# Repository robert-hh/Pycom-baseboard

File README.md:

Baseboard: Simple baseboard for PyCom development modules

This board does not use SMD components. Instead low price modules for the USB/UART
bridge and the SD card adapter are used. The USB/UART bridge is the red FTDI
module, which are sold at prices of $1.5 on. It has to be set to 3.3 V.
The SD card module is the one of Pololu, which is also widely available.
Pictures of the modules are included in the repository. Depending on the
soldered connectors, the board can also be used for WiPy1. Artwork on the board indicates, how the Pycom modules have to be inserted.

The board also carries the two transistor logic used by espressif to switch into
bootstrap mode. The Pycom command line updater pycom-fwtool-cli supports that
with the -r option. The graphical variant does not. If you are building The
firmware yourself, you have to change application.mk at the command for
flashing. Change it into:

  ESPTOOLPY_SERIAL = $(ESPTOOLPY) --port $(ESPPORT) --baud $(ESPBAUD)

especially, remove  "--before no_reset --after no_reset"

Also on the board:
- connections for a reset button, if the board is placed into a closed box.
- A JST2 connector for a battery. There is no charging circuit on the board,
but a diode is foreseen to decouple the battery from the USB/UART bridge. If
you do not need that, solder a wire. Depending on your preference, a Schottky
diode or a silicon diode can be used. Schottky diodes have a substantial
reverse current.  

The metal areas at the mounting holes are connected to GND. That is favorable
if you put the whole board into a metal box, used as ground plane for a Lora or
LTE antenna. If that gets a problem, use Nylon screws.

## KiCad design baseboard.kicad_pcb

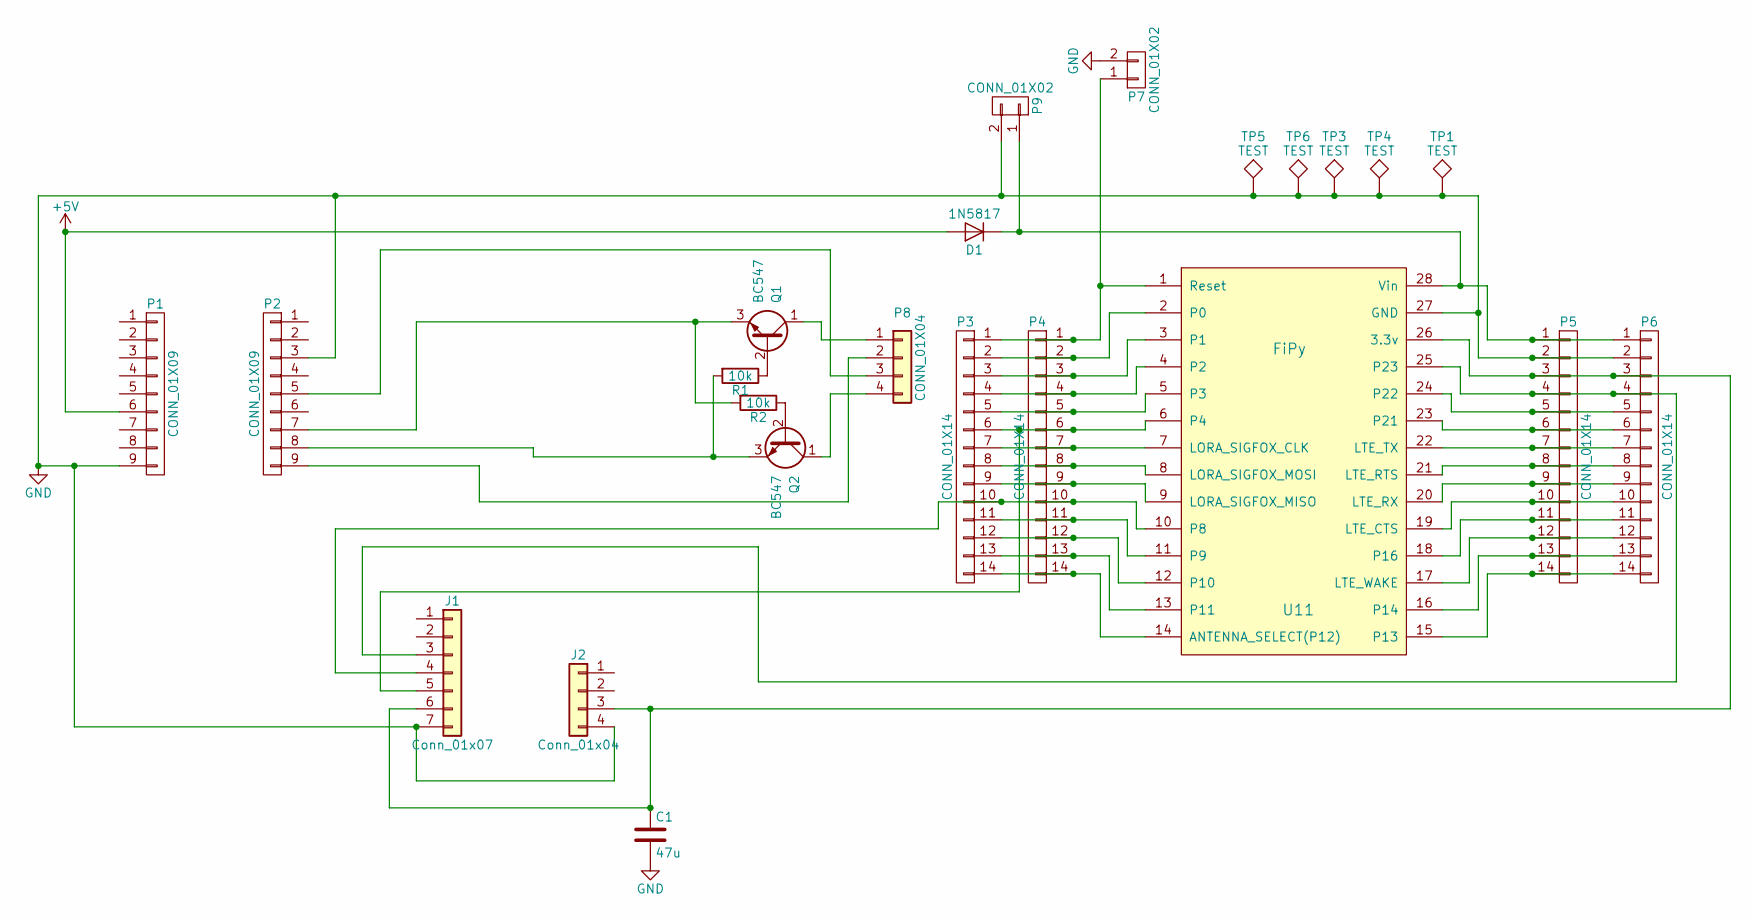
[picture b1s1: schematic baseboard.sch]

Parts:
C1: 47u; CP_Radial_D6.3mm_P2.50mm
D1: 1N5817; D_DO-41_SOD81_P10.16mm_Horizontal
J1: Conn_01x07; Socket_Strip_Straight_1x07_Pitch2.54mm
J2: Conn_01x04; Socket_Strip_Straight_1x04_Pitch2.54mm
P1, P2: CONN_01X09; Socket_Strip_Straight_1x09_Pitch2.54mm
P3, P4, P5, P6: CONN_01X14; Socket_Strip_Straight_1x14_Pitch2.54mm
P7: CONN_01X02; SW_Tactile_SPST_Angled_PTS645Vx58-2LFS
P8: CONN_01X04; Socket_Strip_Straight_1x04_Pitch2.54mm
P9: CONN_01X02; JST_PH_S2B-PH-K_02x2.00mm_Angled
Q1, Q2: BC547; TO-92_Inline_Narrow_Oval
R1, R2: 10k; R_Axial_DIN0207_L6.3mm_D2.5mm_P10.16mm_Horizontal
TP1: TEST; Socket_Strip_Straight_1x01_Pitch2.54mm
TP3, TP4, TP5, TP6: TEST; MountingHole_3.2mm_M3_Pad_Via
U11: FiPy; LoPy_with_headers

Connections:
+5V: D1.2 (A), P1.6
GND: C1.2, J1.7, J2.4, P1.9, P2.3, P5.2, P6.2, P7.2, P9.2, TP1.1, TP3.1, TP4.1, TP5.1, TP6.1, U11.27 (GND)
unnamed: C1.1, J1.6, J2.3, P5.3, P6.3, U11.26 (3.3v)
unnamed: D1.1 (K), P5.1, P6.1, P9.1, U11.28 (Vin)
unnamed: J1.3, P5.4, P6.4, U11.25 (P23)
unnamed: J1.4, P3.10, P4.10, U11.10 (P8)
unnamed: J1.5, P3.6, P4.6, U11.6 (P4)
unnamed: P2.5, P8.3
unnamed: P2.7, Q1.3 (E), R2.2
unnamed: P2.8, Q2.3 (E), R1.2
unnamed: P2.9, P8.2
unnamed: P3.1, P4.1, P7.1, U11.1 (Reset)
unnamed: P3.2, P4.2, U11.2 (P0)
unnamed: P3.3, P4.3, U11.3 (P1)
unnamed: P3.4, P4.4, U11.4 (P2)
unnamed: P3.5, P4.5, U11.5 (P3)
unnamed: P3.7, P4.7, U11.7 (LORA_SIGFOX_CLK)
unnamed: P3.8, P4.8, U11.8 (LORA_SIGFOX_MOSI)
unnamed: P3.9, P4.9, U11.9 (LORA_SIGFOX_MISO)
unnamed: P3.11, P4.11, U11.11 (P9)
unnamed: P3.12, P4.12, U11.12 (P10)
unnamed: P3.13, P4.13, U11.13 (P11)
unnamed: P3.14, P4.14, U11.14 (ANTENNA_SELECT(P12))
unnamed: P5.5, P6.5, U11.24 (P22)
unnamed: P5.6, P6.6, U11.23 (P21)
unnamed: P5.7, P6.7, U11.22 (LTE_TX)
unnamed: P5.8, P6.8, U11.21 (LTE_RTS)
unnamed: P5.9, P6.9, U11.20 (LTE_RX)
unnamed: P5.10, P6.10, U11.19 (LTE_CTS)
unnamed: P5.11, P6.11, U11.18 (P16)
unnamed: P5.12, P6.12, U11.17 (LTE_WAKE)
unnamed: P5.13, P6.13, U11.16 (P14)
unnamed: P5.14, P6.14, U11.15 (P13)
unnamed: P8.1, Q1.1 (C)
unnamed: P8.4, Q2.1 (C)
unnamed: Q1.2 (B), R1.1
unnamed: Q2.2 (B), R2.1

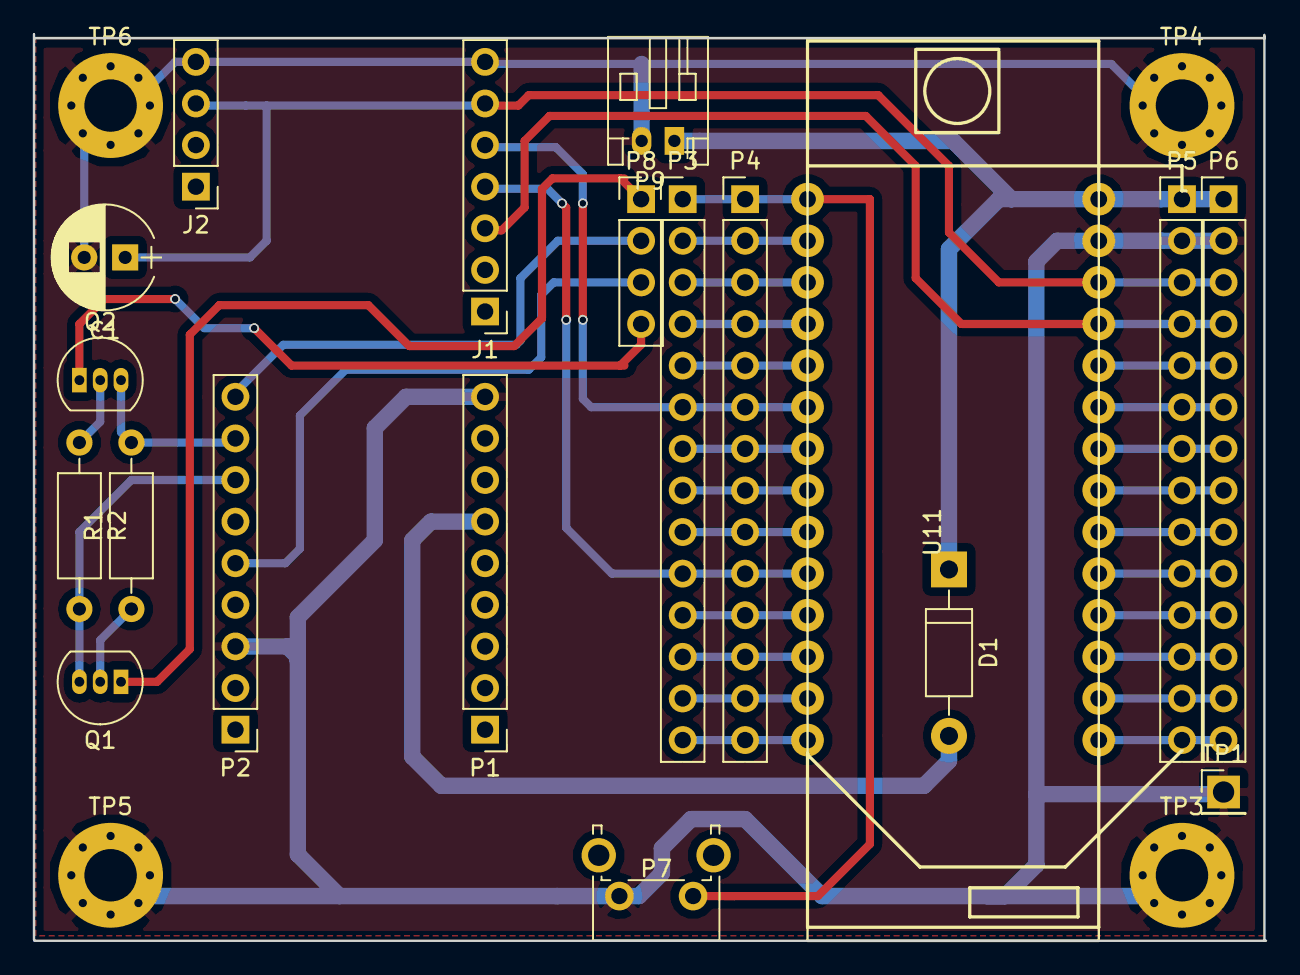
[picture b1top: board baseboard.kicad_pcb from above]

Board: 2 copper layers, 75.2 x 55.4 mm, 23 parts (0 on the bottom side), 37 nets.

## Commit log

2018-09-07 baseboard: Simple baseboard for PyCom development modules
    This board does not use SMD circuits. Instead low price modules for the USB/UART
    bridge and the SD card adapter are used. The USB/UART bridge is the red FTDI
    module, which are sold at prices of $1.5 on. The SD card module is the one of
    Pololu, which is also widely available. Pictures of the modules are included
    in the repository. Depending on the soldered connectors, the board can also
    be used for WiPy1. Artwork on the board indicates, how the Pycom modules have
2018-09-07 README.md: Added
2019-01-21 Some changes after HD reorg:
    - Fixed the -pro file
    - jpg file size change
